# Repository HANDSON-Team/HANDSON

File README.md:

# CYBATHLON-Team-HANDSON-Archive
Archive for the devices used in CYBATHLON by team HANDSON.

https://cybathlon.com/en/teams/handson

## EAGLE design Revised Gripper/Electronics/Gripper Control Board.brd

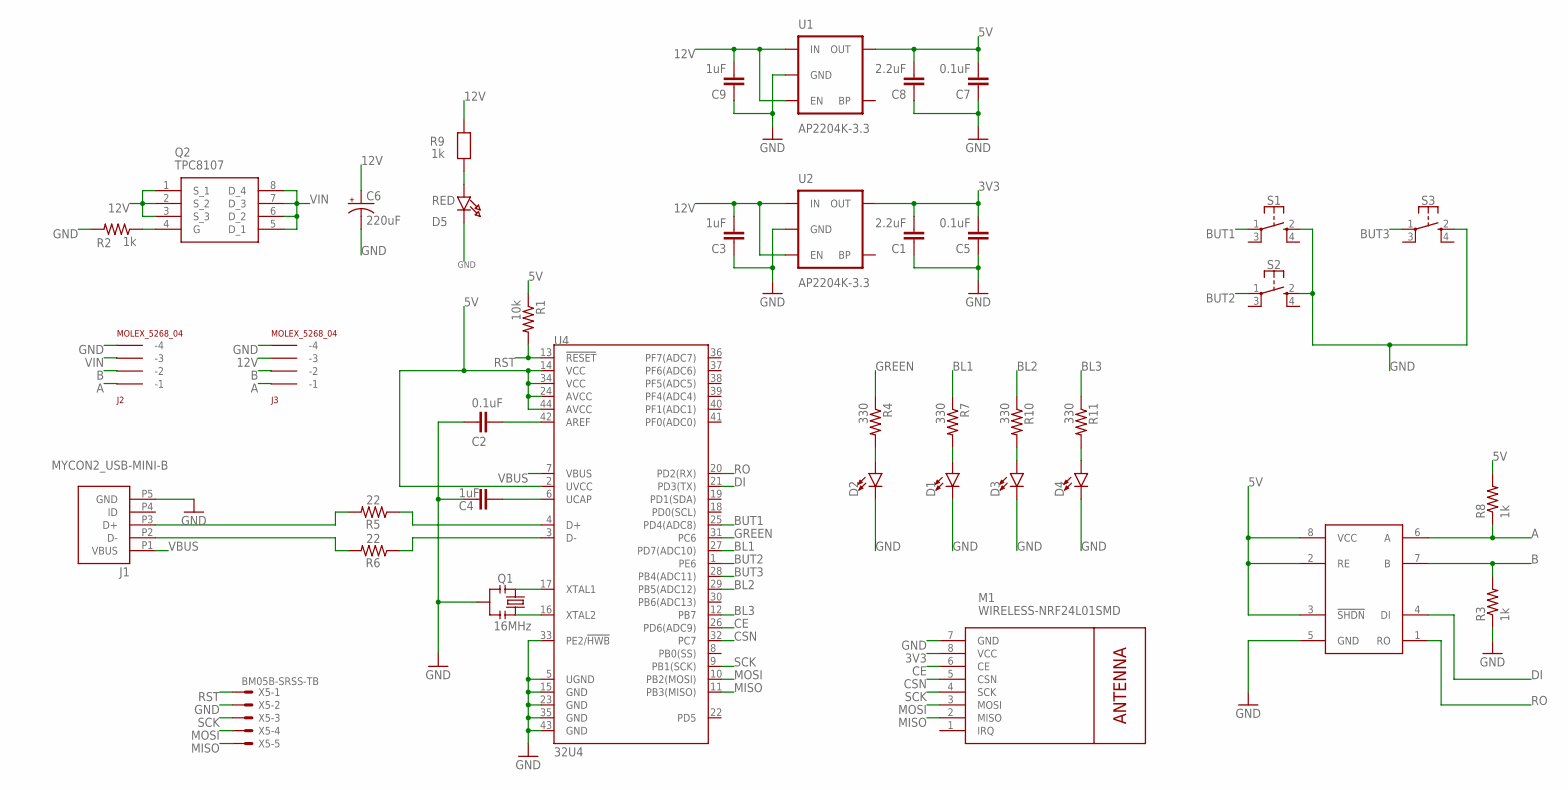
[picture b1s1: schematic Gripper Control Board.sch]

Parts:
C1, C8: 2.2uF; 0603-CAP
C2, C5, C7: 0.1uF; 0603-CAP
C3, C4, C9: 1uF; 0603-CAP
C6: 220uF; PANASONIC_D
D1, D2, D3, D4: LED0603; LED-0603
D5: RED; CHIPLED_0603
J1: MYCON2_USB-MINI-B; CON2_USB_MICRO_B_AT
J2, J3: MOLEX_5268_04; 5267-4
M1: WIRELESS-NRF24L01SMD; WIRELESS-NRF24L01-SMD
Q1: 16MHz; RESONATOR-SMD
Q2: TPC8107; SOIC127P600X175-8N
R1: 10k; 0603-RES
R2: 1k; 0603
R3, R8: 1k; 0603-RES
R4, R7, R10, R11: 330; 0603-RES
R5, R6: 22; 0603-RES
R9: 1k; 0603-MINI
S1, S2, S3: SKSGAAE010; SKSG
U1, U2: AP2204K-3.3; SOT23-5
U3: MAX13487
U4: 32U4; QFN-44-NOPAD
X5: BM05B-SRSS-TB

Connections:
3V3: C1.2, C5.2, M1.8 (VCC), U2.5 (OUT)
5V: C7.2, C8.2, R1.1, R8.2, U1.5 (OUT), U3.2 (RE), U3.3 (!SHDN), U3.8 (VCC), U4.2 (UVCC), U4.14 (VCC), U4.24 (AVCC), U4.34 (VCC), U4.44 (AVCC)
12V: C3.2, C6.+, C9.2, J3.P$3 (-3), Q2.1 (S_1), Q2.2 (S_2), Q2.3 (S_3), R9.2, U1.1 (IN), U1.3 (EN), U2.1 (IN), U2.3 (EN)
A: J2.P$1 (-1), J3.P$1 (-1), R8.1, U3.6 (A)
B: J2.P$2 (-2), J3.P$2 (-2), R3.2, U3.7 (B)
BL1: R7.1, U4.27 (PD7(ADC10))
BL2: R10.1, U4.29 (PB5(ADC12))
BL3: R11.1, U4.12 (PB7)
BUT1: S1.1, U4.25 (PD4(ADC8))
BUT2: S2.1, U4.1 (PE6)
BUT3: S3.1, U4.28 (PB4(ADC11))
CE: M1.6 (CE), U4.26 (PD6(ADC9))
CSN: M1.5 (CSN), U4.32 (PC7)
D1_N: J1.P2 (D-), R6.2
D1_P: J1.P3 (D+), R5.2
D2_N: R6.1, U4.3 (D-)
D2_P: R5.1, U4.4 (D+)
DI: U3.4 (DI), U4.21 (PD3(TX))
GND: C1.1, C2.1, C3.1, C4.1, C5.1, C6.-, C7.1, C8.1, C9.1, D1.C, D2.C, D3.C, D4.C, D5.C, J1.P5 (GND), J2.P$4 (-4), J3.P$4 (-4), M1.7 (GND), Q1.2, R2.2, R3.1, S1.2 (3), S2.2 (3), S3.2 (3), U1.2 (GND), U2.2 (GND), U3.5 (GND), U4.5 (UGND), U4.15 (GND), U4.23 (GND), U4.33 (PE2/!HWB), U4.35 (GND), U4.43 (GND), X5.2
GREEN: R4.1, U4.31 (PC6)
MISO: M1.2 (MISO), U4.11 (PB3(MISO)), X5.5
MOSI: M1.3 (MOSI), U4.10 (PB2(MOSI)), X5.4
unnamed: D2.A, R4.2
unnamed: D1.A, R7.2
unnamed: D3.A, R10.2
unnamed: D4.A, R11.2
unnamed: D5.A, R9.1
unnamed: Q2.4 (G), R2.1
unnamed: C4.2, U4.6 (UCAP)
unnamed: C2.2, U4.42 (AREF)
RO: U3.1 (RO), U4.20 (PD2(RX))
RST: R1.2, U4.13 (!RESET), X5.1
SCK: M1.4 (SCK), U4.9 (PB1(SCK)), X5.3
VBUS: J1.P1 (VBUS), U4.7 (VBUS)
VIN: J2.P$3 (-3), Q2.5 (D_1), Q2.6 (D_2), Q2.7 (D_3), Q2.8 (D_4)
X1: Q1.1, U4.17 (XTAL1)
X2: Q1.3, U4.16 (XTAL2)

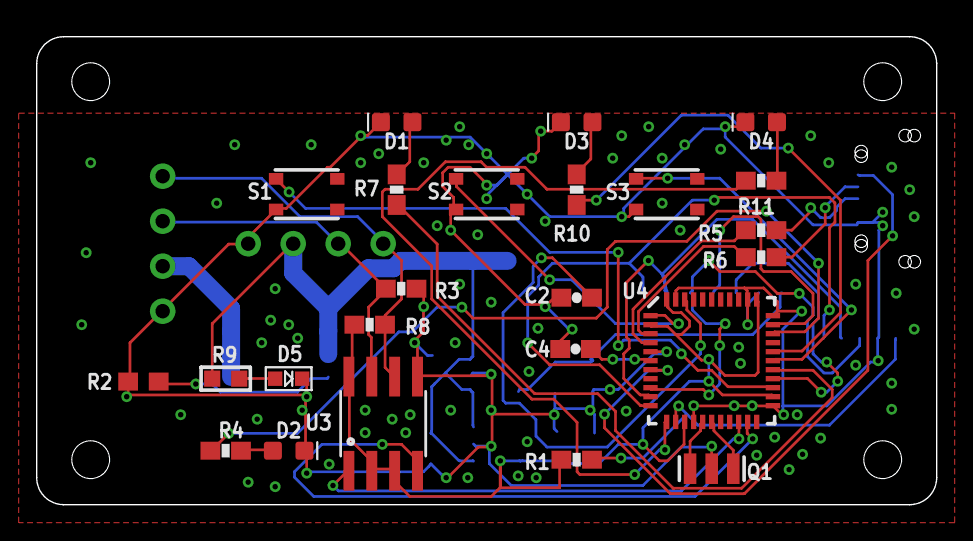
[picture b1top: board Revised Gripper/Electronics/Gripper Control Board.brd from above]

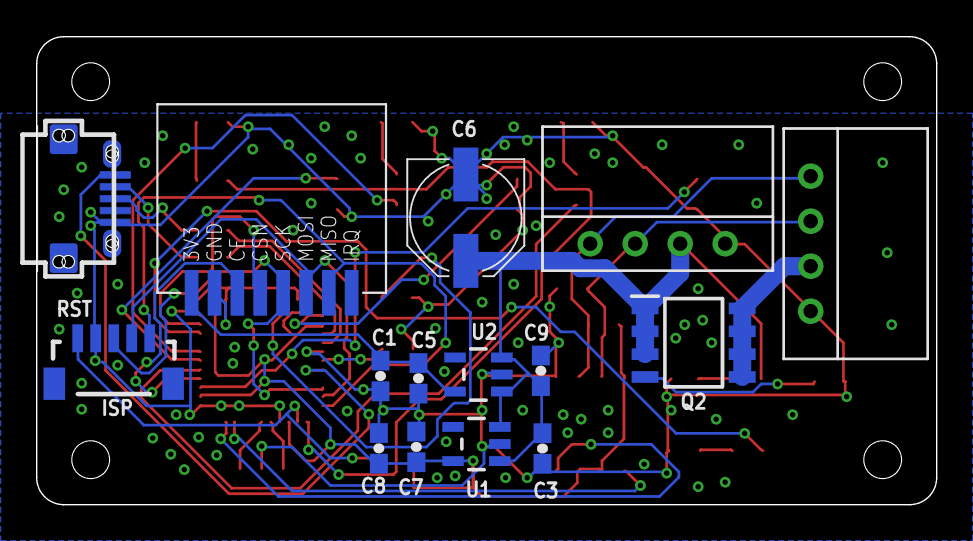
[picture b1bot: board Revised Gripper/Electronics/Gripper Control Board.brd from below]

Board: 2 copper layers, 50.0 x 26.0 mm, 39 parts (15 on the bottom side), 37 nets.

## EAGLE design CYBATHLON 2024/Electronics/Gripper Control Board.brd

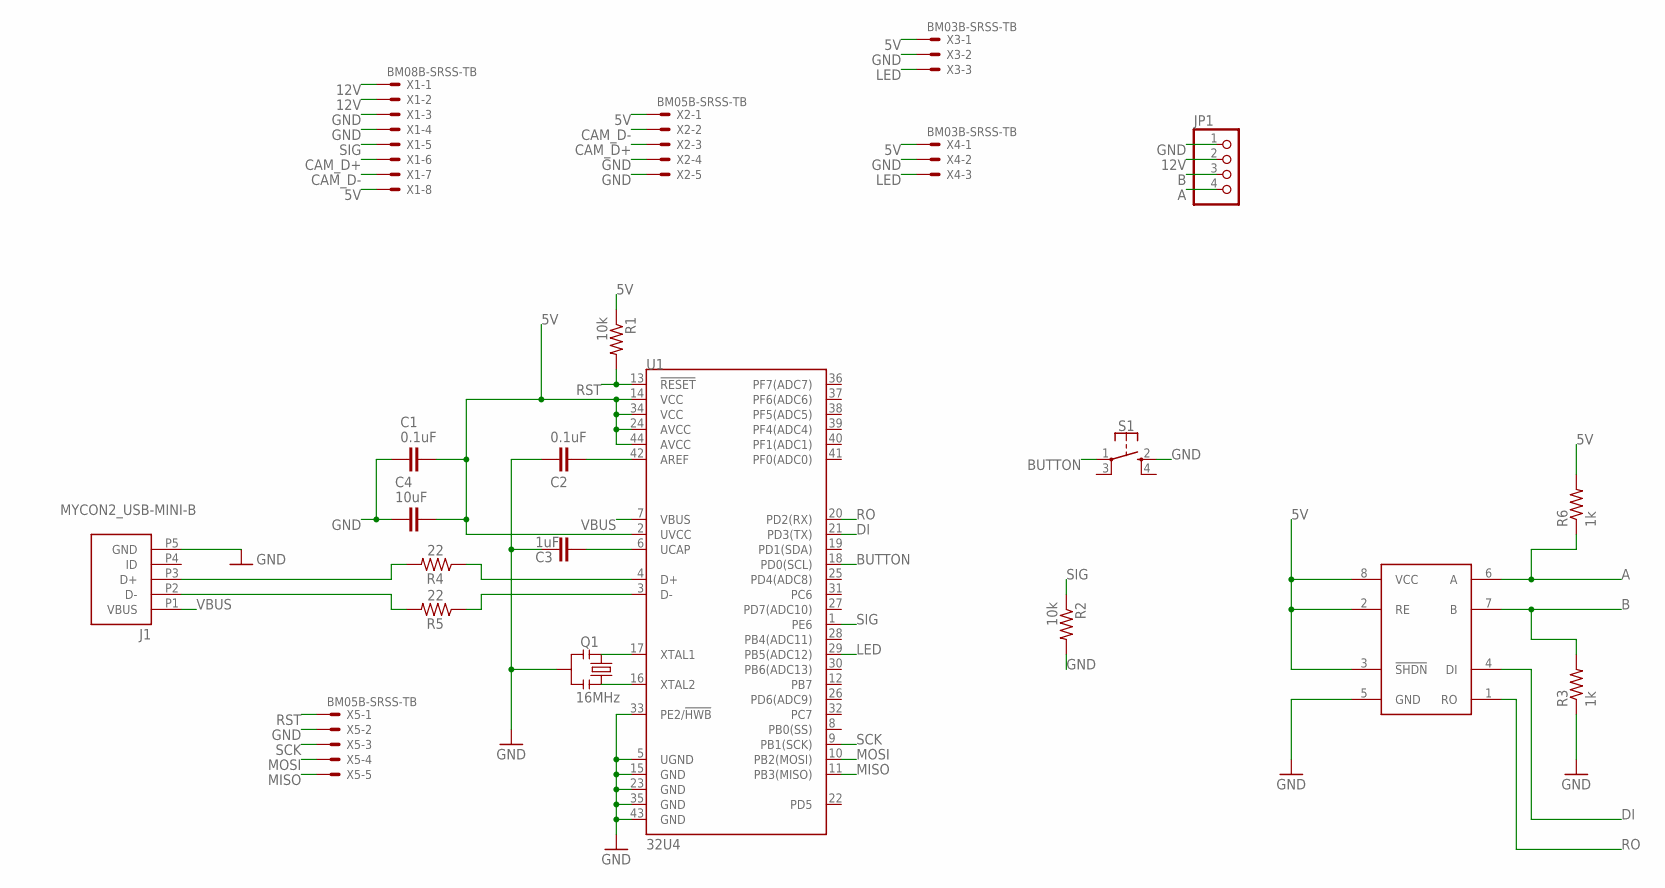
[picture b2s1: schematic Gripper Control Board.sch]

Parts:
C1, C2: 0.1uF; 0603-CAP
C3: 1uF; 0603-CAP
C4: 10uF; 0805
J1: MYCON2_USB-MINI-B; CON2_USB_MICRO_B_AT
JP1: PINHD-1X4; 1X04
Q1: 16MHz; RESONATOR-SMD
R1, R2: 10k; 0603-RES
R3, R6: 1k; 0603-RES
R4, R5: 22; 0603-RES
S1: SKSGAAE010; SKSG
U1: 32U4; QFN-44-NOPAD
U2: MAX13487
X1: BM08B-SRSS-TB
X2, X5: BM05B-SRSS-TB
X3, X4: BM03B-SRSS-TB

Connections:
5V: C1.2, C4.2, R1.1, R6.2, U1.2 (UVCC), U1.14 (VCC), U1.24 (AVCC), U1.34 (VCC), U1.44 (AVCC), U2.2 (RE), U2.3 (!SHDN), U2.8 (VCC), X1.8, X2.1, X3.1, X4.1
12V: JP1.2, X1.1, X1.2
A: JP1.4, R6.1, U2.6 (A)
B: JP1.3, R3.2, U2.7 (B)
BUTTON: S1.1, U1.18 (PD0(SCL))
CAM_D+: X1.6, X2.3
CAM_D-: X1.7, X2.2
DI: U1.21 (PD3(TX)), U2.4 (DI)
GND: C1.1, C2.1, C3.1, C4.1, J1.P5 (GND), JP1.1, Q1.2, R2.2, R3.1, S1.2 (3), U1.5 (UGND), U1.15 (GND), U1.23 (GND), U1.33 (PE2/!HWB), U1.35 (GND), U1.43 (GND), U2.5 (GND), X1.3, X1.4, X2.4, X2.5, X3.2, X4.2, X5.2
LED: U1.29 (PB5(ADC12)), X3.3, X4.3
MISO: U1.11 (PB3(MISO)), X5.5
MOSI: U1.10 (PB2(MOSI)), X5.4
unnamed: R4.1, U1.4 (D+)
unnamed: C3.2, U1.6 (UCAP)
unnamed: R5.1, U1.3 (D-)
unnamed: C2.2, U1.42 (AREF)
unnamed: J1.P3 (D+), R4.2
unnamed: J1.P2 (D-), R5.2
RO: U1.20 (PD2(RX)), U2.1 (RO)
RST: R1.2, U1.13 (!RESET), X5.1
SCK: U1.9 (PB1(SCK)), X5.3
SIG: R2.1, U1.1 (PE6), X1.5
VBUS: J1.P1 (VBUS), U1.7 (VBUS)
X1: Q1.1, U1.17 (XTAL1)
X2: Q1.3, U1.16 (XTAL2)

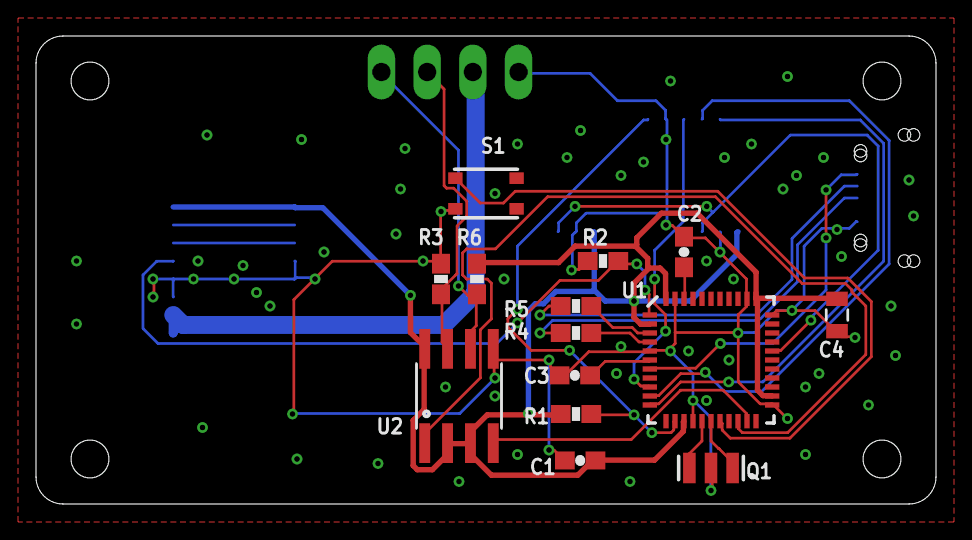
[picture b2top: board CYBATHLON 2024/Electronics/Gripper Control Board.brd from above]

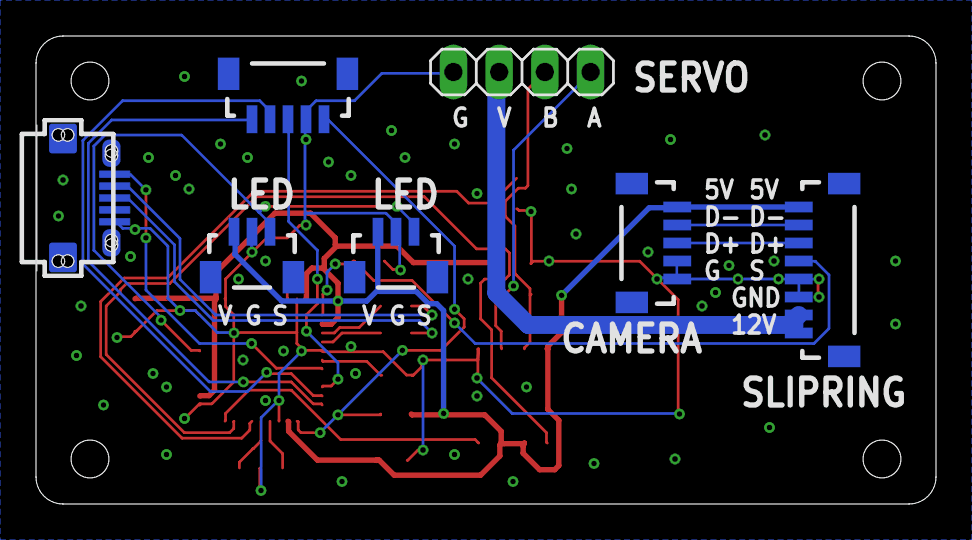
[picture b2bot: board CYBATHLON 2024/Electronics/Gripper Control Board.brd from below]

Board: 2 copper layers, 50.0 x 26.0 mm, 21 parts (7 on the bottom side), 25 nets.

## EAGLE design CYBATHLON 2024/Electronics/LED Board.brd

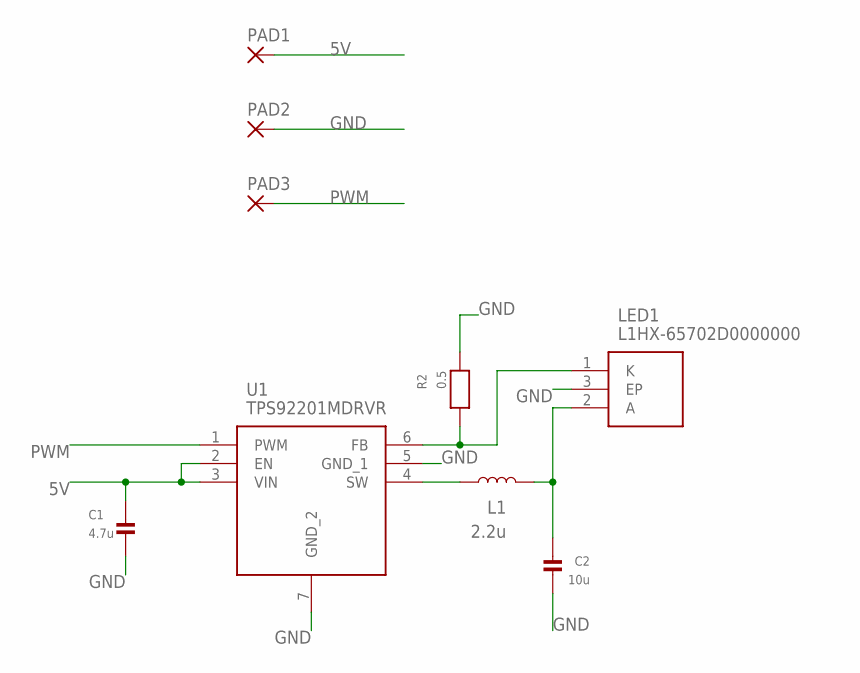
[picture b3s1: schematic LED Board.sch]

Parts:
C1: 4.7u; 0805
C2: 10u; 0805
L1: 2.2u; 1008(2520)
LED1: L1HX-65702D0000000; L1HX65702D0000000
PAD1, PAD2, PAD3: SMD2; SMD1,27-2,54
R2: 0.5; R0603
U1: TPS92201MDRVR; SON65P200X200X80-7N

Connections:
5V: C1.1, PAD1.1, U1.2 (EN), U1.3 (VIN)
GND: C1.2, C2.2, LED1.3 (EP), PAD2.1, R2.2, U1.5 (GND_1), U1.7 (GND_2)
unnamed: L1.1, U1.4 (SW)
unnamed: C2.1, L1.2, LED1.2 (A)
unnamed: LED1.1 (K), R2.1, U1.6 (FB)
PWM: PAD3.1, U1.1 (PWM)

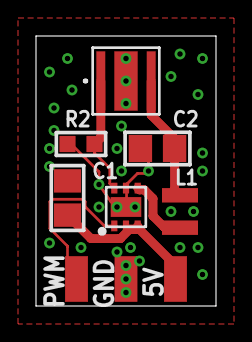
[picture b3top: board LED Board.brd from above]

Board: 2 copper layers, 10.0 x 15.0 mm, 9 parts (0 on the bottom side), 6 nets.

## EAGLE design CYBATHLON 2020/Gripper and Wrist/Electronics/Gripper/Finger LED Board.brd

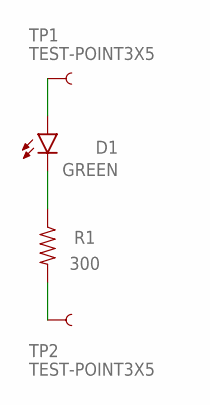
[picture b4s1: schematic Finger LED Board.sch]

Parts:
D1: GREEN; LED-1206
R1: 300; 0603
TP1, TP2: TEST-POINT3X5; PAD.03X.05

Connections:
unnamed: D1.C, R1.1
unnamed: R1.2, TP2.P$1
unnamed: D1.A, TP1.P$1

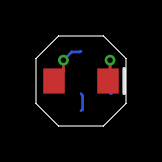
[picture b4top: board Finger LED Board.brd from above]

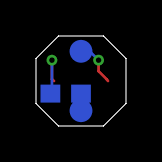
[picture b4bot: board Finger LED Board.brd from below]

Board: 2 copper layers, 5.0 x 5.0 mm, 4 parts (3 on the bottom side), 3 nets.

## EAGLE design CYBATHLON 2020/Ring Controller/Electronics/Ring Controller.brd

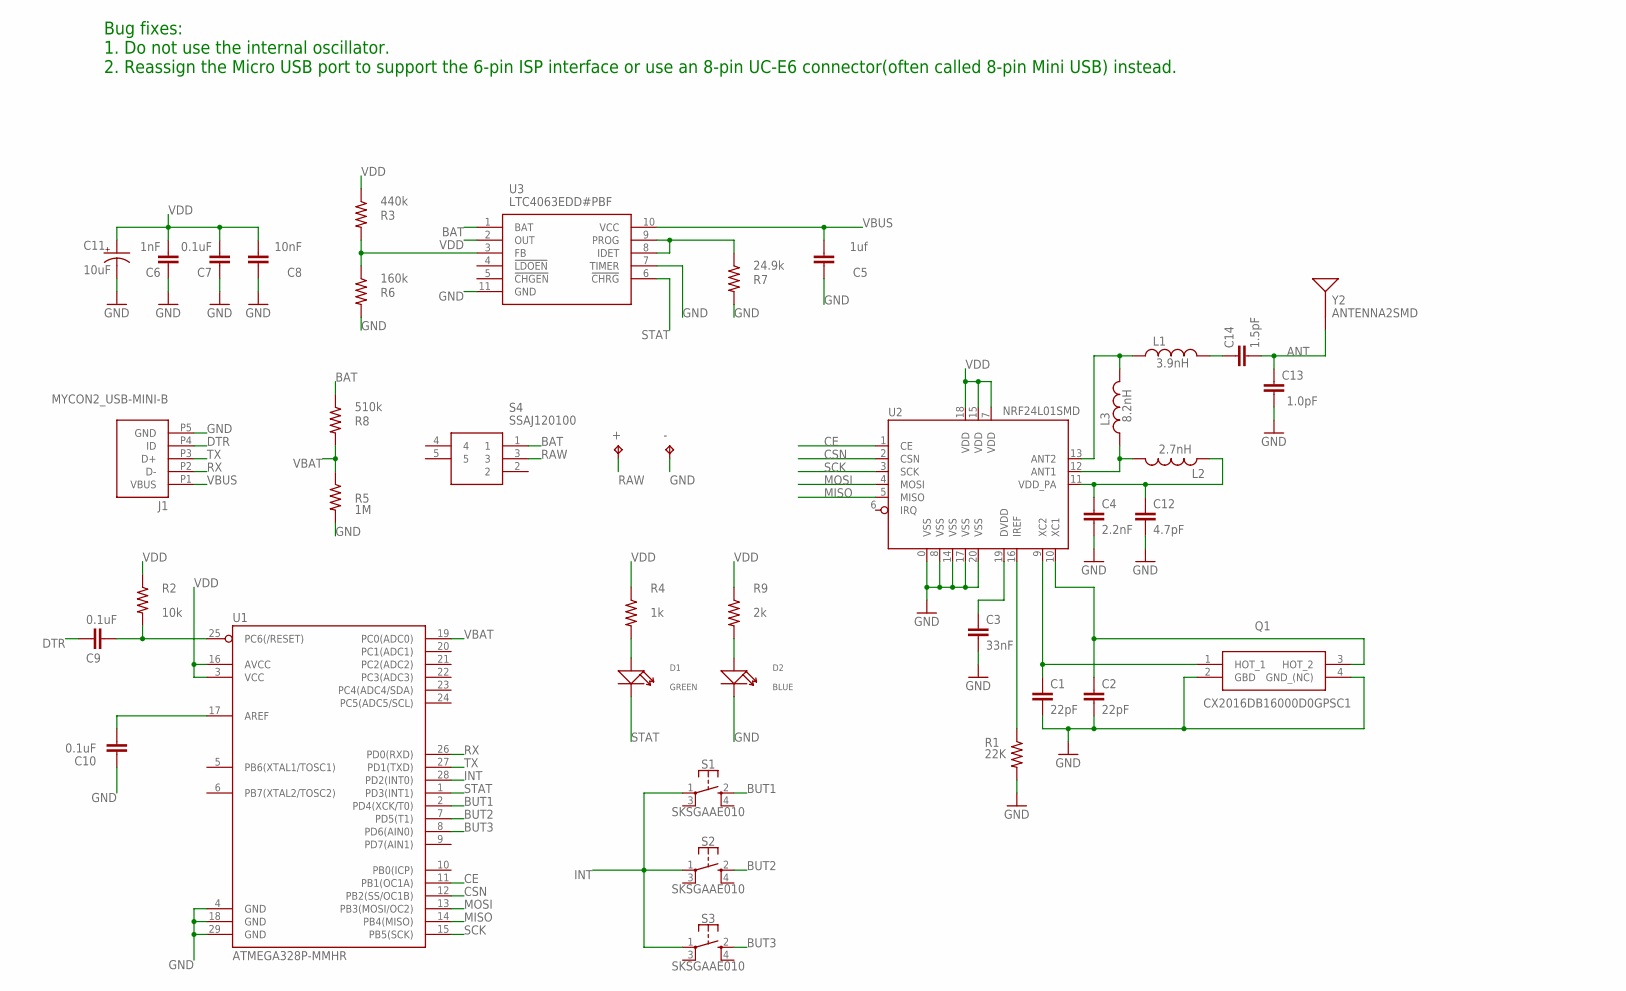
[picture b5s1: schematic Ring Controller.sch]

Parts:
+: TPB1,27; B1,27
-: TPB1,27; B1,27
C1, C2: 22pF; 0402-CAP
C3: 33nF; 0402-CAP
C4: 2.2nF; 0402-CAP
C5: 1uf; 0402-CAP
C6: 1nF; 0402-CAP
C7, C9, C10: 0.1uF; 0402-CAP
C8: 10nF; 0402-CAP
C11: 10uF; 0603-POLAR
C12: 4.7pF; 0402-CAP
C13: 1.0pF; 0402-CAP
C14: 1.5pF; 0402-CAP
D1: GREEN; LED-0402
D2: BLUE; LED-0402
J1: MYCON2_USB-MINI-B; CON2_USB_MICRO_B_AT
L1: 3.9nH; C0402
L2: 2.7nH; C0402
L3: 8.2nH; C0402
Q1: CX2016DB16000D0GPSC1; CX2016DB_1
R1: 22K; 0402-RES
R2: 10k; 0402-RES
R3: 440k; 0402-RES
R4: 1k; 0402-RES
R5: 1M; 0402-RES
R6: 160k; 0402-RES
R7: 24.9k; 0402-RES
R8: 510k; 0402-RES
R9: 2k; 0402-RES
S1, S2, S3: SKSGAAE010; SKSG
S4: SSAJ120100
U1: ATMEGA328P-MMHR; QFN45P400X400X100-29N
U2: NRF24L01SMD; QFN20-4X4MM
U3: LTC4063EDD#PBF; SON50P300X300X80-11N
Y2: ANTENNA2SMD; ANTENNA-CHIP2

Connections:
ANT: C13.2, C14.2, Y2.FEED
BAT: R8.1, S4.1, U3.1 (BAT)
BUT1: S1.2 (3), U1.2 (PD4(XCK/T0))
BUT2: S2.2 (3), U1.7 (PD5(T1))
BUT3: S3.2 (3), U1.8 (PD6(AIN0))
CE: U1.11 (PB1(OC1A)), U2.1 (CE)
CSN: U1.12 (PB2(SS/OC1B)), U2.2 (CSN)
DTR: C9.1, J1.P4 (ID)
GND: -.TP, C1.2, C2.2, C3.2, C4.2, C5.1, C6.1, C7.1, C8.1, C10.1, C11.-, C12.2, C13.1, D2.-, J1.P5 (GND), Q1.2 (GBD), Q1.4 (GND_(NC)), R1.2, R5.2, R6.2, R7.2, U1.4 (GND), U1.18 (GND), U1.29 (GND), U2.0 (VSS), U2.8 (VSS), U2.14 (VSS), U2.17 (VSS), U2.20 (VSS), U3.7 (TIMER), U3.11 (GND)
INT: S1.1, S2.1, S3.1, U1.28 (PD2(INT0))
MISO: U1.14 (PB4(MISO)), U2.5 (MISO)
MOSI: U1.13 (PB3(MOSI/OC2)), U2.4 (MOSI)
unnamed: C1.1, Q1.1 (HOT_1), U2.9 (XC2)
unnamed: C2.1, Q1.3 (HOT_2), U2.10 (XC1)
unnamed: L2.2, L3.1, U2.12 (ANT1)
unnamed: R1.1, U2.16 (IREF)
unnamed: C3.1, U2.19 (DVDD)
unnamed: L1.1, L3.2, U2.13 (ANT2)
unnamed: C4.1, C12.1, L2.1, U2.11 (VDD_PA)
unnamed: D1.+, R4.2
unnamed: D2.+, R9.2
unnamed: C14.1, L1.2
unnamed: C10.2, U1.17 (AREF)
unnamed: R3.2, R6.1, U3.3 (FB)
unnamed: R7.1, U3.8 (IDET), U3.9 (PROG)
RAW: +.TP, S4.3
RST: C9.2, R2.2, U1.25 (PC6(/RESET))
RX: J1.P2 (D-), U1.26 (PD0(RXD))
SCK: U1.15 (PB5(SCK)), U2.3 (SCK)
STAT: D1.-, U1.1 (PD3(INT1)), U3.6 (!CHRG)
TX: J1.P3 (D+), U1.27 (PD1(TXD))
VBAT: R5.1, R8.2, U1.19 (PC0(ADC0))
VBUS: C5.2, J1.P1 (VBUS), U3.10 (VCC)
VDD: C6.2, C7.2, C8.2, C11.+, R2.1, R3.1, R4.1, R9.1, U1.3 (VCC), U1.16 (AVCC), U2.7 (VDD), U2.15 (VDD), U2.18 (VDD), U3.2 (OUT)

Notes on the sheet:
Bug fixes: 1. Do not use the internal oscillator. 2. Reassign the Micro USB port to support the 6-pin ISP interface or use an 8-pin UC-E6 connector(often called 8-pin Mini USB) instead.

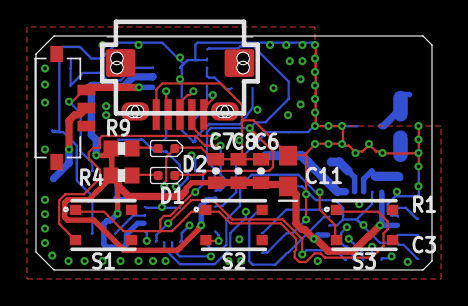
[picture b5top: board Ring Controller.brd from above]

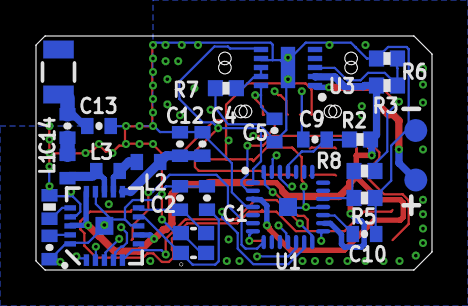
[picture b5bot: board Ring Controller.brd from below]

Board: 4 copper layers, 22.0 x 13.0 mm, 40 parts (27 on the bottom side), 34 nets.

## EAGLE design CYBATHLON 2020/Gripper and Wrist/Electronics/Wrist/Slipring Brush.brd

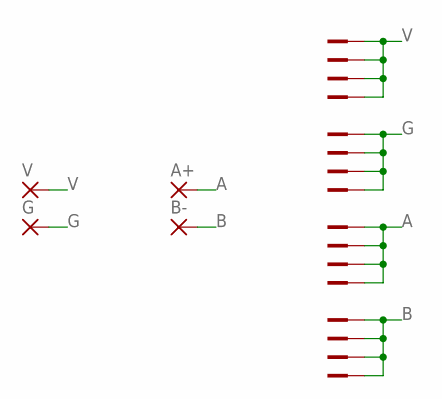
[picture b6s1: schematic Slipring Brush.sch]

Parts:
A+: SMD2; SMD1,27-2,54
B-: SMD2; SMD1,27-2,54
G: SMD2; SMD1,27-2,54
U$1, U$2, U$3, U$4, U$5, U$6, U$7, U$8, U$9, U$10, U$11, U$12, U$13, U$14, U$15, U$16: POGOPIN_A585
V: SMD2; SMD1,27-2,54

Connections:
A: A+.1, U$9.P$1, U$9.P$2, U$9.P$3, U$10.P$1, U$10.P$2, U$10.P$3, U$11.P$1, U$11.P$2, U$11.P$3, U$12.P$1, U$12.P$2, U$12.P$3
B: B-.1, U$13.P$1, U$13.P$2, U$13.P$3, U$14.P$1, U$14.P$2, U$14.P$3, U$15.P$1, U$15.P$2, U$15.P$3, U$16.P$1, U$16.P$2, U$16.P$3
G: G.1, U$5.P$1, U$5.P$2, U$5.P$3, U$6.P$1, U$6.P$2, U$6.P$3, U$7.P$1, U$7.P$2, U$7.P$3, U$8.P$1, U$8.P$2, U$8.P$3
V: U$1.P$1, U$1.P$2, U$1.P$3, U$2.P$1, U$2.P$2, U$2.P$3, U$3.P$1, U$3.P$2, U$3.P$3, U$4.P$1, U$4.P$2, U$4.P$3, V.1

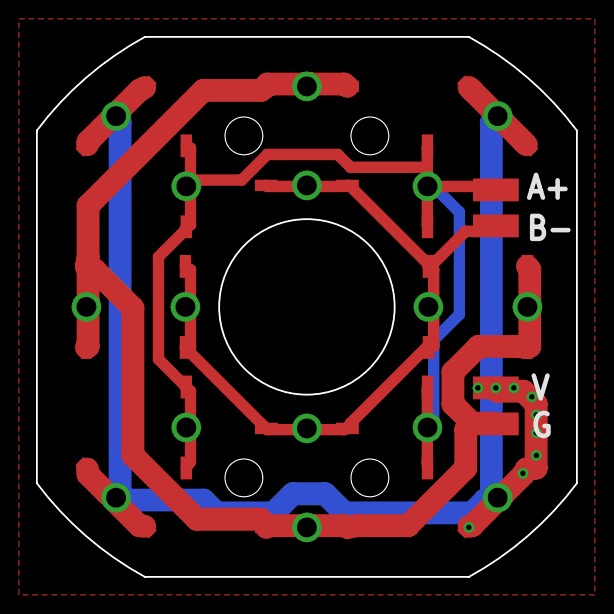
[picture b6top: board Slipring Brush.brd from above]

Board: 2 copper layers, 30.0 x 30.0 mm, 20 parts (0 on the bottom side), 4 nets.

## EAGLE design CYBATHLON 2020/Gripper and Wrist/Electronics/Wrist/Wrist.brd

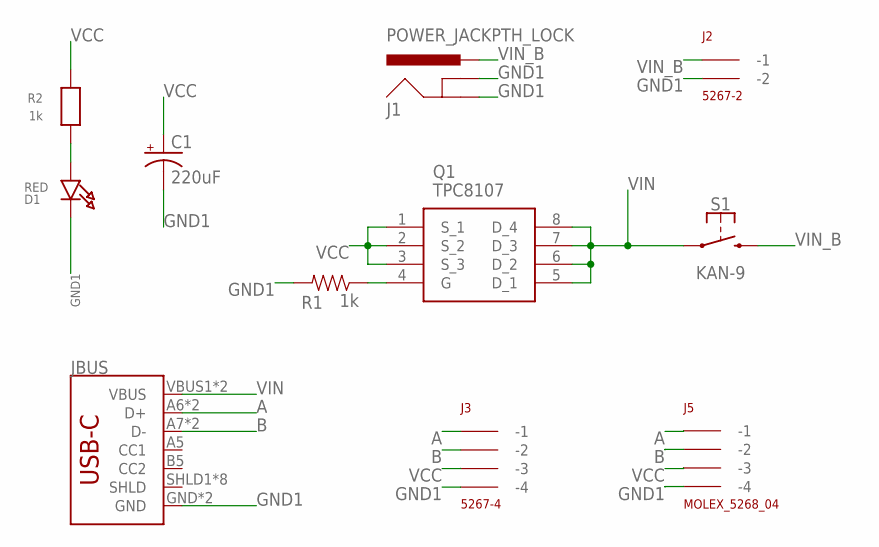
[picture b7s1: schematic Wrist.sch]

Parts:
C1: 220uF; PANASONIC_D
D1: RED; CHIPLED_0603
J1: POWER_JACKPTH_LOCK; POWER_JACK_PTH_LOCK
J2: 5267-2
J3: 5267-4
J5: MOLEX_5268_04; 5267-4
JBUS: USB_C16PIN; USB-C-16P
Q1: TPC8107; SOIC127P600X175-8N
R1: 1k; 0603
R2: 1k; 0603-MINI
S1: KAN-9

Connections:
A: J3.P$1 (-1), J5.P$1 (-1), JBUS.A6 (D+), JBUS.B6 (D+)
B: J3.P$2 (-2), J5.P$2 (-2), JBUS.A7 (D-), JBUS.B7 (D-)
GND1: C1.-, D1.C, J1.GND, J1.GNDBREAK, J2.P$2 (-2), J3.P$4 (-4), J5.P$4 (-4), JBUS.GND, JBUS.GND2 (GND), R1.2
unnamed: D1.A, R2.1
unnamed: Q1.4 (G), R1.1
VCC: C1.+, J3.P$3 (-3), J5.P$3 (-3), Q1.1 (S_1), Q1.2 (S_2), Q1.3 (S_3), R2.2
VIN: JBUS.VBUS1 (VBUS), JBUS.VBUS2 (VBUS), Q1.5 (D_1), Q1.6 (D_2), Q1.7 (D_3), Q1.8 (D_4), S1.P$1 (1)
VIN_B: J1.PWR, J2.P$1 (-1), S1.P$2 (3)

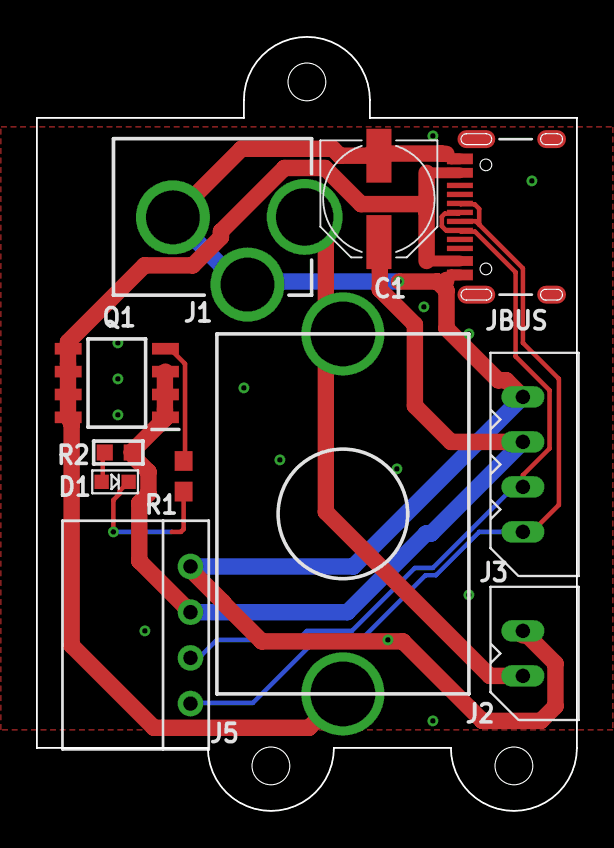
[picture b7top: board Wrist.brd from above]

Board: 2 copper layers, 30.0 x 43.0 mm, 11 parts (0 on the bottom side), 8 nets.

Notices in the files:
parts and their libraries:
SparkFun-LED: Licensing: Creative Commons ShareAlike 4.0 International - https://creativecommons.org/licenses/by-sa/4.0
SFE Aesthetics: Licensing: CC v3.0 Share-Alike You are welcome to use this library for commercial purposes.
